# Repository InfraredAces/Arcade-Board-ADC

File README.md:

# Arcade Board ADC

This project is hardware and firmare designed to convert 0-3.3V analog input signals to digital output signals for gamepad controller boards. 

It is built with the intention of using Hall Effect keyboard switches with controller boards that typically only accept digital signals for gamepad inputs through 20 pin connectors. Such as

- [RP2040 Advanced Breakout Board](https://github.com/OpenStickCommunity/Hardware/tree/main/Boards/GP2040-CE%20Official%20Boards/RP2040%20Advanced%20Breakout%20Board/RP2040%20Advanced%20Breakout%20Board%20-%20Passthrough) ([GP2040-CE](https://gp2040-ce.info/))
-  [Brook Universal Fighting Board](https://www.brookaccessory.com/detail/06960737/)
-  [Brook UFB-Fusion](https://www.brookaccessory.com/products/ufbfusion/index.html)
-  [Brook P5 PLUS Fighting Board](https://www.brookaccessory.com/products/p5plus/index.html)

## To-Do

- [X] User Configurable GPIO Input
- [X] Custom Actuation Distance
- [ ] Advanced Trigger Behavior
  - [X] Static Trigger
  - [ ] Rapid Trigger
  - [ ] Continuous Rapid Trigger
- [ ] Per Button Settings
- [ ] Analog output for Left/Right Analog stick axes
- [ ] Analog output for L2/R2 Analog Triggers
- [ ] Analog output for all gamepad inputs
- [ ] Board Hardware - Production Files
  - [ ] Primary Board
  - [ ] MUX Auxilary Board
- [ ] Web GUI Configurator
- [ ] Github Workflow .uf2 Build (CI/CD)

## Project Setup

### Debian/Ubuntu

Set up Pico SDK

```shell
git clone https://github.com/raspberrypi/pico-sdk.git
RUN cd pico-sdk && git submodule update --init

# Set the PICO_SDK_PATH environment variable to where you just cloned the repo above.
export PICO_SDK_PATH=/path/to/pico-sdk
```

Install the toolchain needed to build Pico projects.

```shell
sudo apt update && apt install -y --no-install-recommends git ca-certificates make cmake gcc g++ gcc-arm-none-eabi libnewlib-arm-none-eabi libstdc++-arm-none-eabi-newlib python3 python3-venv nodejs npm clang
```

### VS Code + Dev Container (Docker)

Use Microsoft's [documentation](https://code.visualstudio.com/docs/devcontainers/tutorial) on running Visual Studio Code in a Docker container using the Dev Containers extension.

The Dockerfile included in the repo will be sufficient for building this project.

## Build Project

Run the following commands in the root of the repo.

```shell
mkdir build
cd build
cmake ..
make
```

## Customize Configuration

### GPIO Output

Edit the header file `config/gpio_output_config.h`

### Gamepad Input Mapping

Edit the configuration files below in `config/CD74HC4067SM96` depending on how many CD74HC4067SM96 you are using and which pins are being used specifically, both of the RP2040 and of the CD74HC4067SM96.

- `config/CD74HC4067SM96/CD74HC4067SM96_00_config.h`
- `config/CD74HC4067SM96/CD74HC4067SM96_01_config.h`
- `config/CD74HC4067SM96/CD74HC4067SM96_02_config.h`
- `config/CD74HC4067SM96/CD74HC4067SM96_03_config.h`

For each of the above configuration files, you will want to modify the following `#define` to prior to building the firmware.

- Set `CD74HC4067SM96_##_ENABLED` to `true` to enable that CD74HC4067SM96 module where `##` is the number of the CD74HC4067SM96 number (i.e. `CD74HC4067SM96_00_config` is CD74HC4067SM96 00)
- Set the Analog GPIO pin (GP26-GP29)
- Set a `ButtonAction` for each `CD74HC4067SM96_##_AA_ACTION` where `##` is the number of the CD74HC4067SM96 number and `AA`is the CD74HC4067SM96 (i.e. `CD74HC4067SM96_00_15_ACTION` is the pin 15 of CD74HC4067SM96 00)

#### ButtonActions

| ButtonAction            | GP2040 | Xinput | Switch  | PS3/4/5  | Dinput | Arcade |
|:------------------------|:-------|:-------|:--------|:---------|:-------|:-------|
| NONE                    | NONE   | NONE   | NONE    | NONE     | NONE   | NONE   |
| BUTTON_PRESS_DPAD_UP    | UP     | UP     | UP      | UP       | UP     | UP     |
| BUTTON_PRESS_DPAD_DOWN  | DOWN   | DOWN   | DOWN    | DOWN     | DOWN   | DOWN   |
| BUTTON_PRESS_DPAD_LEFT  | RIGHT  | RIGHT  | RIGHT   | RIGHT    | RIGHT  | RIGHT  |
| BUTTON_PRESS_DPAD_RIGHT | LEFT   | LEFT   | LEFT    | LEFT     | LEFT   | LEFT   |
| BUTTON_PRESS_LS_UP      |        |        |         |          |        |        |
| BUTTON_PRESS_LS_DOWN    |        |        |         |          |        |        |
| BUTTON_PRESS_LS_LEFT    |        |        |         |          |        |        |
| BUTTON_PRESS_LS_RIGHT   |        |        |         |          |        |        |
| BUTTON_PRESS_RS_UP      |        |        |         |          |        |        |
| BUTTON_PRESS_RS_DOWN    |        |        |         |          |        |        |
| BUTTON_PRESS_RS_LEFT    |        |        |         |          |        |        |
| BUTTON_PRESS_RS_RIGHT   |        |        |         |          |        |        |
| BUTTON_PRESS_B1         | B1     | A      | B       | Cross    | 2      | K1     |
| BUTTON_PRESS_B2         | B2     | B      | A       | Circle   | 3      | K2     |
| BUTTON_PRESS_B3         | B3     | X      | Y       | Square   | 1      | P1     |
| BUTTON_PRESS_B4         | B4     | Y      | X       | Triangle | 4      | P2     |
| BUTTON_PRESS_L1         | L1     | LB     | L       | L1       | 5      | P4     |
| BUTTON_PRESS_R1         | R1     | RB     | R       | R1       | 6      | P3     |
| BUTTON_PRESS_L2         | L2     | LT     | ZL      | L2       | 7      | K4     |
| BUTTON_PRESS_R2         | R2     | RT     | ZR      | R2       | 8      | K3     |
| BUTTON_PRESS_S1         | S1     | Back   | Minus   | Select   | 9      | Coin   |
| BUTTON_PRESS_S2         | S2     | Start  | Plus    | Start    | 10     | Start  |
| BUTTON_PRESS_A1         | A1     | Guide  | Home    | PS       | 13     | NONE   |
| BUTTON_PRESS_A2         | A2     | NONE   | Capture | NONE     | 14     | NONE   |
| BUTTON_PRESS_L3         | L3     | LS     | LS      | L3       | 11     | LS     |
| BUTTON_PRESS_R3         | R3     | RS     | RS      | R3       | 12     | RS     |

## Acknowledgements

- [GP2040-CE] - Inspiration for creating the project and making great gamepad firmware

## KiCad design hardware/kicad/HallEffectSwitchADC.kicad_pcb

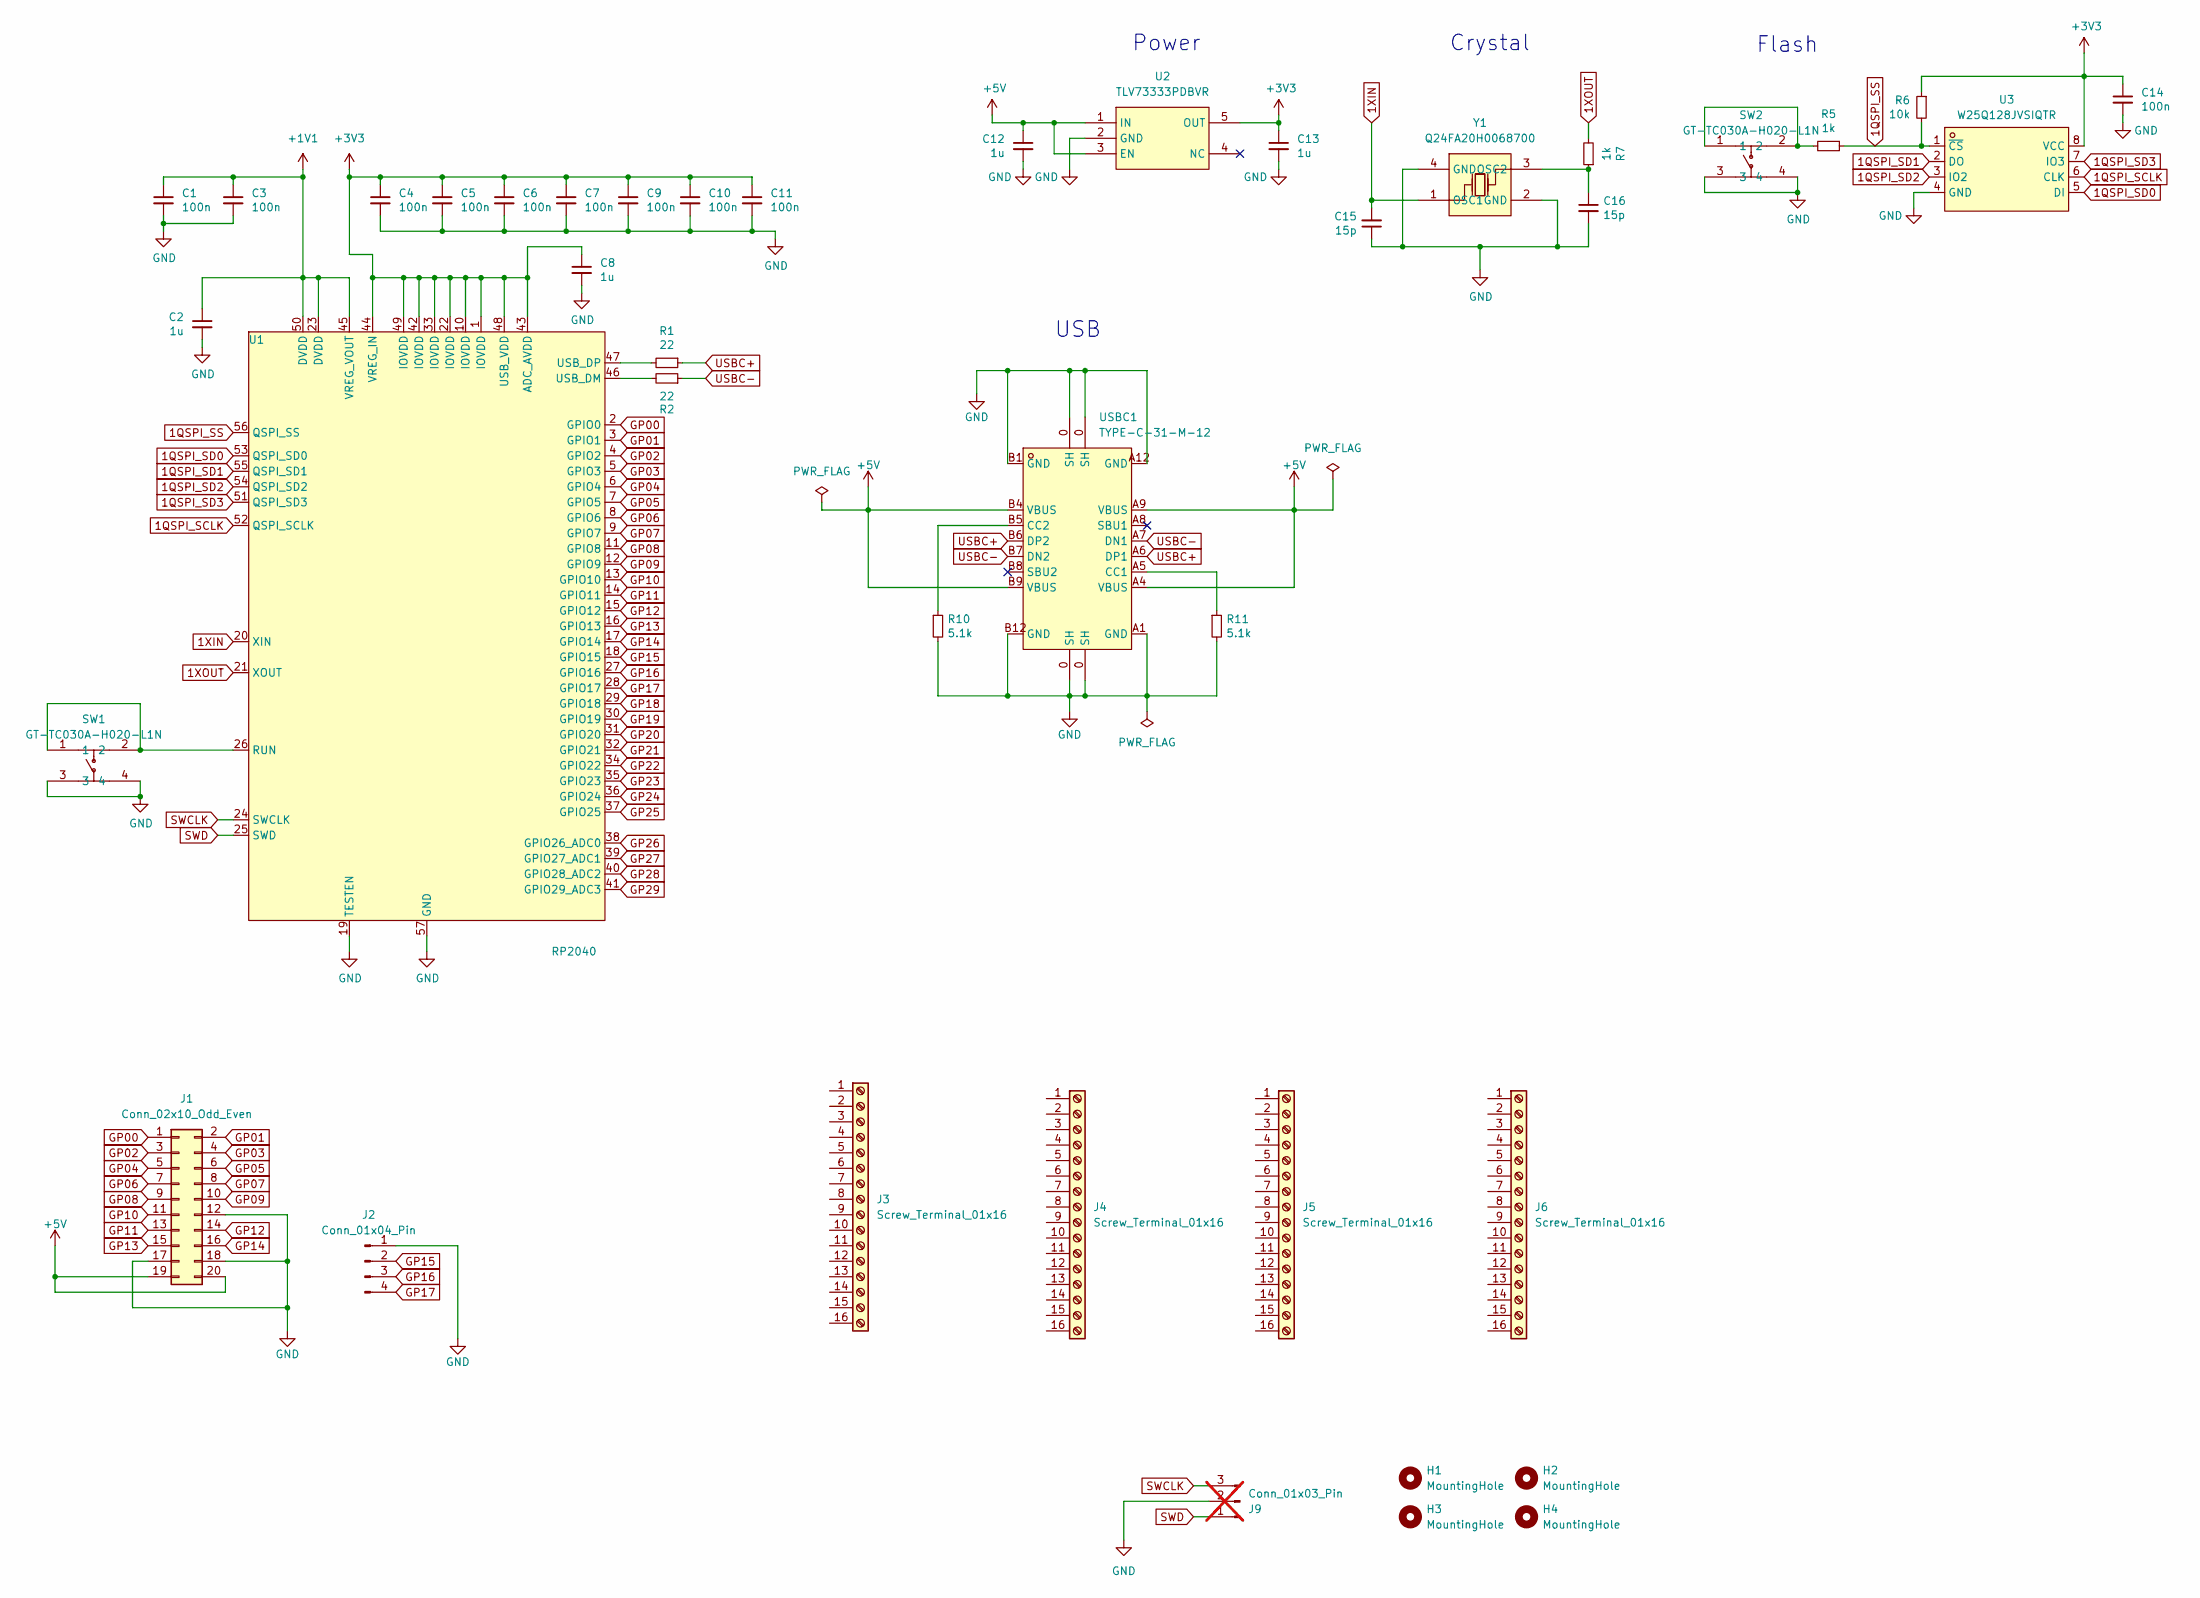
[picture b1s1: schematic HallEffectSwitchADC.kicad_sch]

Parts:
C1, C3, C4, C5, C6, C7, C9, C10, C11, C14: 100n; C_0402_1005Metric; LCSC C1525
C2, C8, C12, C13: 1u; C_0402_1005Metric; LCSC C52923
C15, C16: 15p; C_0402_1005Metric; LCSC C1548
H1, H2, H3, H4: MountingHole; MountingHole_2.2mm_M2
J1: Conn_02x10_Odd_Even; PinSocket_2x10_P2.54mm_Vertical
J2: Conn_01x04_Pin; PinHeader_1x04_P2.54mm_Horizontal
J3, J4, J5, J6: Screw_Terminal_01x16; PinSocket_1x16_P2.54mm_Vertical
J9: Conn_01x03_Pin; PinHeader_1x03_P2.54mm_Vertical; not fitted
R1, R2: 22; R_0402_1005Metric; LCSC C25092
R5, R7: 1k; R_0402_1005Metric; LCSC C11702
R6: 10k; R_0402_1005Metric; LCSC C25744
R10, R11: 5.1k; R_0402_1005Metric; LCSC C25905
SW1, SW2: GT-TC030A-H020-L1N; SW-SMD_4P-L3.6-W3.0-P1.50-LS4.7; LCSC Part C843670
U1: RP2040; LQFN-56_L7.0-W7.0-P0.4-EP; LCSC C2040
U2: TLV73333PDBVR; SOT-23-5_L3.0-W1.7-P0.95-LS2.8-BR; LCSC Part C134139
U3: W25Q128JVSIQTR; SOIC-8_L5.3-W5.3-P1.27-LS8.0-BL; LCSC Part C97521
USBC1: TYPE-C-31-M-12; USB-C_SMD-TYPE-C-31-M-12; LCSC Part C165948
Y1: Q24FA20H0068700; CRYSTAL-SMD_4P-L2.5-W2.0-BL; LCSC Part C90603

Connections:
1QSPI_SCLK: U1.52 (QSPI_SCLK), U3.6 (CLK)
1QSPI_SD0: U1.53 (QSPI_SD0), U3.5 (DI)
1QSPI_SD1: U1.55 (QSPI_SD1), U3.2 (DO)
1QSPI_SD2: U1.54 (QSPI_SD2), U3.3 (IO2)
1QSPI_SD3: U1.51 (QSPI_SD3), U3.7 (IO3)
1QSPI_SS: R5.1, R6.2, U1.56 (QSPI_SS), U3.1 (~CS)
1XIN: C15.2, U1.20 (XIN), Y1.1 (OSC1)
1XOUT: R7.2, U1.21 (XOUT)
+1V1: C1.1, C2.1, C3.1, U1.23 (DVDD), U1.45 (VREG_VOUT), U1.50 (DVDD)
+3V3: C4.1, C5.1, C6.1, C7.1, C8.1, C9.1, C10.1, C11.1, C13.1, C14.1, R6.1, U1.1 (IOVDD), U1.10 (IOVDD), U1.22 (IOVDD), U1.33 (IOVDD), U1.42 (IOVDD), U1.43 (ADC_AVDD), U1.44 (VREG_IN), U1.48 (USB_VDD), U1.49 (IOVDD), U2.5 (OUT), U3.8 (VCC)
+5V: C12.1, J1.19, J1.20, U2.1 (IN), U2.3 (EN), USBC1.A4 (VBUS), USBC1.A9 (VBUS), USBC1.B4 (VBUS), USBC1.B9 (VBUS)
GND: C1.2, C2.2, C3.2, C4.2, C5.2, C6.2, C7.2, C8.2, C9.2, C10.2, C11.2, C12.2, C13.2, C14.2, C15.1, C16.2, J1.12, J1.17, J1.18, J2.1, J9.2, R10.2, R11.2, SW1.3, SW1.4, SW2.3, SW2.4, U1.19 (TESTEN), U1.57 (GND), U2.2 (GND), U3.4 (GND), USBC1.0 (SH), USBC1.A1 (GND), USBC1.A12 (GND), USBC1.B1 (GND), USBC1.B12 (GND), Y1.2 (GND), Y1.4 (GND)
GP00: J1.1, U1.2 (GPIO0)
GP01: J1.2, U1.3 (GPIO1)
GP02: J1.3, U1.4 (GPIO2)
GP03: J1.4, U1.5 (GPIO3)
GP04: J1.5, U1.6 (GPIO4)
GP05: J1.6, U1.7 (GPIO5)
GP06: J1.7, U1.8 (GPIO6)
GP07: J1.8, U1.9 (GPIO7)
GP08: J1.9, U1.11 (GPIO8)
GP09: J1.10, U1.12 (GPIO9)
GP10: J1.11, U1.13 (GPIO10)
GP11: J1.13, U1.14 (GPIO11)
GP12: J1.14, U1.15 (GPIO12)
GP13: J1.15, U1.16 (GPIO13)
GP14: J1.16, U1.17 (GPIO14)
GP15: J2.2, U1.18 (GPIO15)
GP16: J2.3, U1.27 (GPIO16)
GP17: J2.4, U1.28 (GPIO17)
GP18: U1.29 (GPIO18)
GP19: U1.30 (GPIO19)
GP20: U1.31 (GPIO20)
GP21: U1.32 (GPIO21)
GP22: U1.34 (GPIO22)
GP23: U1.35 (GPIO23)
GP24: U1.36 (GPIO24)
GP25: U1.37 (GPIO25)
GP26: U1.38 (GPIO26_ADC0)
GP27: U1.39 (GPIO27_ADC1)
GP28: U1.40 (GPIO28_ADC2)
GP29: U1.41 (GPIO29_ADC3)
unnamed: R5.2, SW2.1, SW2.2
unnamed: SW1.1, SW1.2, U1.26 (RUN)
unnamed: R2.2, U1.46 (USB_DM)
unnamed: R1.2, U1.47 (USB_DP)
unnamed: R11.1, USBC1.A5 (CC1)
unnamed: R10.1, USBC1.B5 (CC2)
unnamed: C16.1, R7.1, Y1.3 (OSC2)
SWCLK: J9.3, U1.24 (SWCLK)
SWD: J9.1, U1.25 (SWD)
USBC+: R1.1, USBC1.A6 (DP1), USBC1.B6 (DP2)
USBC-: R2.1, USBC1.A7 (DN1), USBC1.B7 (DN2)

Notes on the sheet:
Power
Crystal
Flash
USB

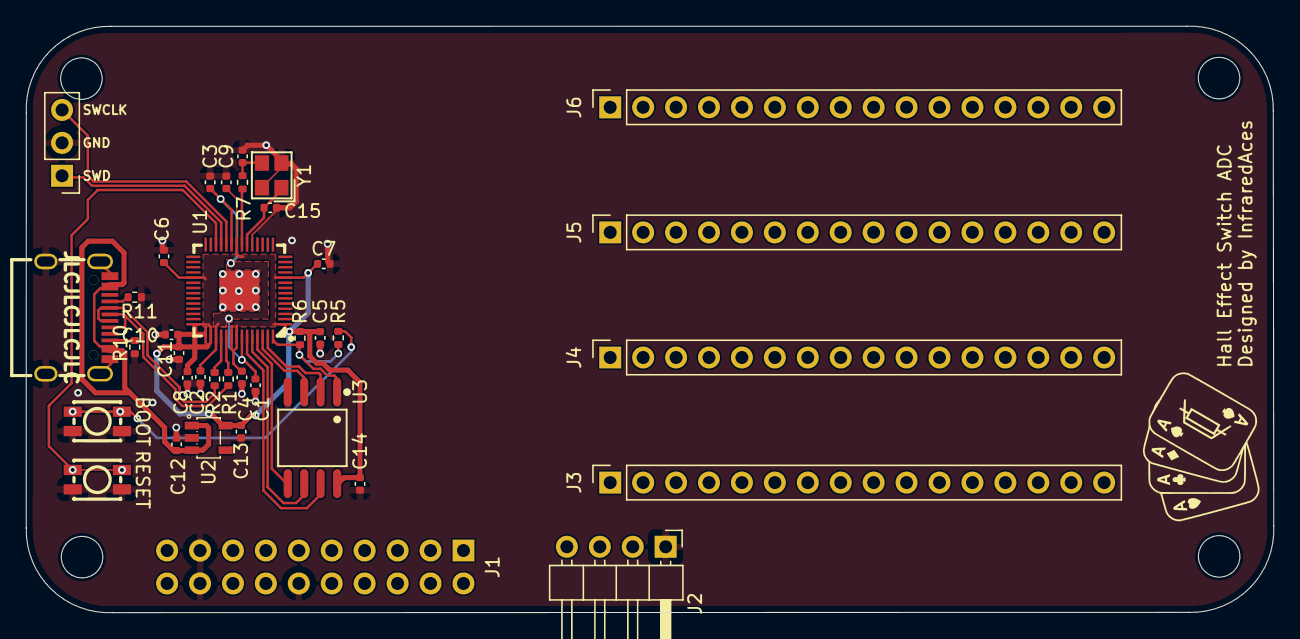
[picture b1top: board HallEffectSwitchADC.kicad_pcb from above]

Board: 2 copper layers, 96.2 x 45.2 mm, 41 parts (1 on the bottom side), 41 nets.

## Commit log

2024-09-07 Add skeleton executables and CMake files
2024-10-17 Add VS Code Dev Container config
2024-10-17 Add VS Code Config
2024-10-17 Add general helper header files
2024-10-17 Add CD74HC4067SM96 driver functionality
2024-10-17 Add CD74HC4067SM96 configs
2024-10-17 Add GPIO output configuration
2024-10-17 Add basic CD74HC4067SM96 and Analog Sensor implementation, Add CMake build process
2024-10-19 Update GPIO config
2024-10-19 Add basic GPIO Out functionality
2024-10-26 Remove vscode and devcontainer files
2024-10-26 Add input configuration
2024-10-26 Add README content
2024-11-04 Update GPIO Output
2024-11-04 Add SMA Filter Library
2024-11-04 Add Kicad to .gitignore
2024-11-04 Add acknowledgements
2024-11-04 Add PCB files
2024-11-04 Add additional Kicad gitignore
2024-11-05 Add Feature Roadmap to README.md
2024-12-30 Update ubuntu version and add ssh to dockerfile
2024-12-30 Refactor for separate demux input and mux output
